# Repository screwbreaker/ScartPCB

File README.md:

# ScartPCB
A little PCB to buld a SCART cable for console and old computers

### Summary
This is a little PCB made to make easy to assemble a SCART cable for console and old computers.

### History
As anyone else I always made my SCART cables by hand, using THT components. And by soldering them directly on the SCART connector.
And that's pefectly fine. Except for systems like the Mega Drive, that require a lot of componets to be fitted in a small space.
So I thought to build a little PCB that fit inside the SCART connector in oder to make everything more easy and clean.

As example here a comparison between my old handmade cable, and the new one with this PCB:

Of course, there are other project like this around. But none of them have all the stuff I wanted.
My requirements was a buffer for the csync and a boost converter for the 12V.

My original plan was to make a PCB for each console.
But, I managed this PCB in a way that can be used almost in any case.
With this PCB is possible to make a SCART cable for almost every console and computer. It is pretty versatile.
And is made to fit inside the cheapest SCART connectors available online.

### Basic informations
The components value in the schematic and in the BOM are for a PAL Mega Drive.
For other systems, refer to the SCART diagram of the secific system.

### How it work
The PCB allow to put components in series and in parallel with the signals.
This allow to use this PCB to buld almost any SCART cable for almost any system.

To make a Mega Drive cable is necessary to put a 220uF capacitor in series with the RGB signals, since is really complicated to find small, and cheap SMD capacitors of this value, the PCB allow to put multiple capacitors in parallel. So, to make a 220uF capacitor is possible to put two 100uF 1206 plus one 22uF 0603.
Probably the 22uF are not really required, but I found the space for some extra footprint in the PCB, so the total value can be easily adjusted.

For example to make a SNES cable put a 0 ohm resistor in place of RR1, RG1, RB1, and place a 75 ohm resitor to ground on each singal by using RR2, RG2, RB2.

If you have a mono audio, like in the first model of Mega Drive, is possible to close the MONO jumper, this short toghether the left and right channel.

The video buffer is there mostly for the Mega Drive, it is nor required on most of the other systems.
To bypass the video buffer, close the NOBUF jumper, in this case do not populate any components on the buffer section.

The RGB jumper can be left open on systems that don't have an RGB output, like a C64.

In general, choose the components to match what do you need to make your video cable. By using 0 ohm resistors as jumper is possible to make almost any combination.

### Csync buffer
The Mega Drive have a problem with the csync signal.
The csync is connected to the input pin of the encoder, not to the output pin.
This can cause some issue on some TV sets. That's why I placed a buffer on the line.

The csync on the Mega Drive is also a TTL level signal, to compensate this a 300-470 ohm reistor can be placed in series with the signal to reduce the voltage to something more like to the standard.
Most of the time also a 220uF capacitor in series with the signal is required.
Not only the Mega Drive use a TTL signal on the csync, it cab be present also on other systems.

Unfortunately not all TV do like this values for the csync line.
So, the values can be adjusted to match your TV set requirements.
Be careful with the level of the signals, they must be in a range that do not cause any damage to your TV.

The values on the csync line, that are on the schematic or in the BOM are for a PAL Mega Drive.
With this set of components I can use my modded MD on my TV, by switching from PAL to NTSC withouth any issue.

Other systems don't have this issue.
The buffer can be bypassed if not needed by closing the NOBUF jumper.
In this case, do not populate any component on the buffer section.

### 12V booster
There is a little boost converter to step up the 5V and get the 12V required for the 4:3 aspect ration.
This is the only way to have the switch voltage.
Some systems, like Amiga or SNES do have the 12V on the connector. But, due to the small space on the PCB, is not possible to use it.

### BOM
The BOM is for a PAL Mega Drive.
To make SCART cables for other system choose the components according to the specific schematic.
Use 0 ohm resistors as jumper where needed.

For the boost converter TPS61040DBVR and TPS61041DBVR are equivalent for this application.

For the buffer any pair of complementary transistors can be used, the package must be SC-70 or equivalent.

### PCB Manufacturing
Unfortunately, due to the space constraints inside the SCART connector, this PCB is a 4 layer board.
And for the same reason, some components are 0402.

The PCB still very cheap to produce, since it is very small, and it use standard vias and traces.

Soldering 0402 components by hand require a bit of skill on soldering.

### Bonus
All the SCART connectors I bought have an hawful issue. The cable gland, the plastic thing that close the SCART shell, is made out the most brittle material in the world.
Initially, I thought that this was because I bought the cheapest SCART connector available on internet.
However even the ones bought on trusth resellers or on electronic shops have this issue.
So, I made a replacement that can be 3D printed. It's far to be perfect, I have no skills on 3D printing. But it do the job.

### License
The PCBs are under the CERN OHL license.
The firmwares, under the GPL3.

This is an OPEN project.
So, like any other project like this, the hope is that others can improve it an reshare with the community.
Don't go out this basic guideline.

### Disclaimer
The hardware and the software are provided to you 'as is' and without any express or implied warranties whatsoever with respect to its functionality, operability or use, including, without limitation, any implied warranties of merchantability, fitness for a particular purpose or infringement. We expressly disclaim any liability whatsoever for any direct, indirect, consequential, incidental or special damages, including, without limitation, lost revenues, lost profits, losses resulting from business interruption or loss of data, regardless of the form of action or legal theory under which the liability may be asserted, even if advised of the possibility or likelihood of such damages.

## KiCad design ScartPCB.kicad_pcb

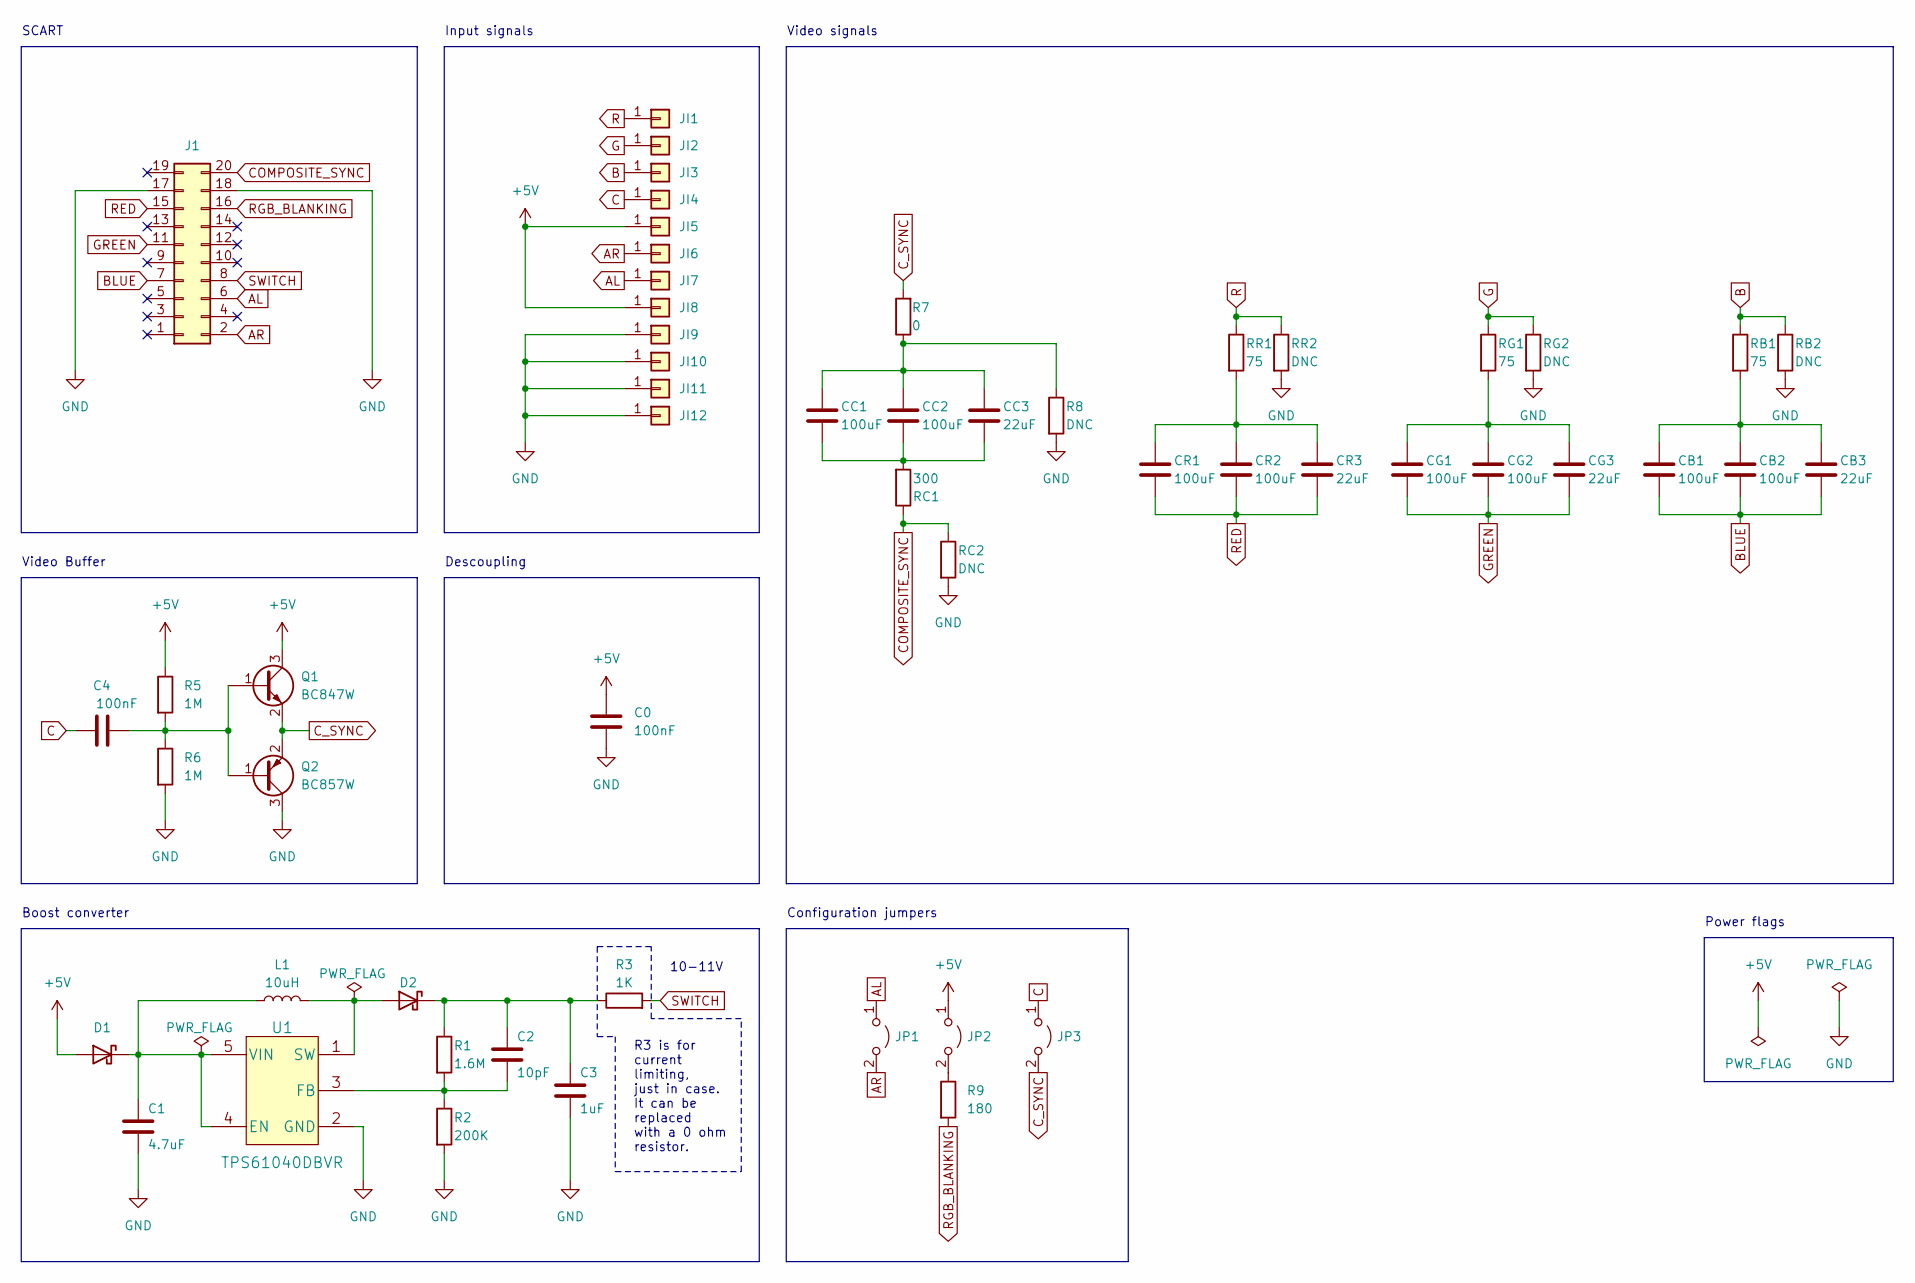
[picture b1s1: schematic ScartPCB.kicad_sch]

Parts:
C0, C4: 100nF; C_0402_1005Metric; Manufacturer_Part_Number CC0402KRX7R7BB104
C1: 4.7uF; C_0402_1005Metric; Manufacturer_Part_Number CM05X5R475M25AH
C2: 10pF; C_0402_1005Metric; Manufacturer_Part_Number 0402N100J500CT
C3: 1uF; C_0402_1005Metric; Manufacturer_Part_Number GRM155R61E105MA12D
CB1, CB2: 100uF; C_1206_3216Metric; Manufacturer_Part_Number GRM31CR61A107ME05L
CB3: 22uF; C_0603_1608Metric; Manufacturer_Part_Number CL10A226MP8NUNE
CC1, CC2: 100uF; C_1206_3216Metric; Manufacturer_Part_Number GRM31CR61A107ME05L
CC3: 22uF; C_0603_1608Metric; Manufacturer_Part_Number CL10A226MP8NUNE
CG1, CG2: 100uF; C_1206_3216Metric; Manufacturer_Part_Number GRM31CR61A107ME05L
CG3: 22uF; C_0603_1608Metric; Manufacturer_Part_Number CL10A226MP8NUNE
CR1, CR2: 100uF; C_1206_3216Metric; Manufacturer_Part_Number GRM31CR61A107ME05L
CR3: 22uF; C_0603_1608Metric; Manufacturer_Part_Number CL10A226MP8NUNE
D1, D2: D_Schottky; D_0402_1005Metric; Manufacturer_Part_Number CDBQR0130R-HF
J1: Conn_02x10_Odd_Even; SCART
JI1, JI2, JI3, JI4, JI5, JI6, JI7, JI8, JI9, JI10, JI11, JI12: Conn_01x01; PAD2x2
JP1, JP2, JP3: Jumper_2_Open; SolderJumper-2_P1.3mm_Open_TrianglePad1.0x1.5mm
L1: 10uH; L_0603_1608Metric; Manufacturer_Part_Number MLZ1608M100WT000
Q1: BC847W; SOT-323_SC-70; Manufacturer_Part_Number BC847W,115
Q2: BC857W; SOT-323_SC-70; Manufacturer_Part_Number BC857W,135
R1: 1.6M; R_0402_1005Metric; Manufacturer_Part_Number RC0402FR-071M6L
R2: 200K; R_0402_1005Metric; Manufacturer_Part_Number 0402WGF2003TCE
R3: 1K; R_0402_1005Metric; Manufacturer_Part_Number 0402WGF1001TCE
R5, R6: 1M; R_0402_1005Metric; Manufacturer_Part_Number 0402WGF1004TCE
R7: 0; R_0402_1005Metric; Manufacturer_Part_Number 0402WGF750JTCE
R8: DNC; R_0402_1005Metric
R9: 180; R_0402_1005Metric; Manufacturer_Part_Number HP02WAF1800TCE
RB1: 75; R_0402_1005Metric; Manufacturer_Part_Number 0402WGF750JTCE
RB2: DNC; R_0402_1005Metric; Manufacturer_Part_Number 0402WGF750JTCE
RC1: 300; R_0402_1005Metric; Manufacturer_Part_Number RC0402JR-07300RL
RC2: DNC; R_0402_1005Metric
RG1: 75; R_0402_1005Metric; Manufacturer_Part_Number 0402WGF750JTCE
RG2: DNC; R_0402_1005Metric; Manufacturer_Part_Number 0402WGF750JTCE
RR1: 75; R_0402_1005Metric; Manufacturer_Part_Number 0402WGF750JTCE
RR2: DNC; R_0402_1005Metric; Manufacturer_Part_Number 0402WGF750JTCE
U1: TPS61040DBVR; Manufacturer_Part_Number TPS61040DBVR

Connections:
+5V: C0.1, D1.2 (A), JI5.1, JI8.1, JP2.1 (A), Q1.3 (C), R5.1
AL: J1.6, JI7.1, JP1.1 (A)
AR: J1.2, JI6.1, JP1.2 (B)
B: JI3.1, RB1.1, RB2.1
BLUE: CB1.2, CB2.2, CB3.2, J1.7
C: C4.1, JI4.1, JP3.1 (A)
COMPOSITE_SYNC: J1.20, RC1.1, RC2.1
C_SYNC: JP3.2 (B), Q1.2 (E), Q2.2 (E), R7.2
G: JI2.1, RG1.1, RG2.1
GND: C0.2, C1.2, C3.2, J1.17, J1.18, JI9.1, JI10.1, JI11.1, JI12.1, Q2.3 (C), R2.2, R6.2, R8.2, RB2.2, RC2.2, RG2.2, RR2.2, U1.2 (GND)
GREEN: CG1.2, CG2.2, CG3.2, J1.11
unnamed: C1.1, D1.1 (K), L1.1, U1.4 (EN), U1.5 (VIN)
unnamed: C2.1, C3.1, D2.1 (K), R1.1, R3.1
unnamed: C2.2, R1.2, R2.1, U1.3 (FB)
unnamed: C4.2, Q1.1 (B), Q2.1 (B), R5.2, R6.1
unnamed: CB1.1, CB2.1, CB3.1, RB1.2
unnamed: CC1.1, CC2.1, CC3.1, RC1.2
unnamed: CC1.2, CC2.2, CC3.2, R7.1, R8.1
unnamed: CG1.1, CG2.1, CG3.1, RG1.2
unnamed: CR1.1, CR2.1, CR3.1, RR1.2
unnamed: D2.2 (A), L1.2, U1.1 (SW)
unnamed: JP2.2 (B), R9.1
R: JI1.1, RR1.1, RR2.1
RED: CR1.2, CR2.2, CR3.2, J1.15
RGB_BLANKING: J1.16, R9.2
SWITCH: J1.8, R3.2

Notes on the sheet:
Configuration jumpers
Power flags
Boost converter
Descoupling
Video Buffer
SCART
Input signals
10-11V
Video signals
R3 is for current limiting, just in case. It can be replaced with a 0 ohm resistor.

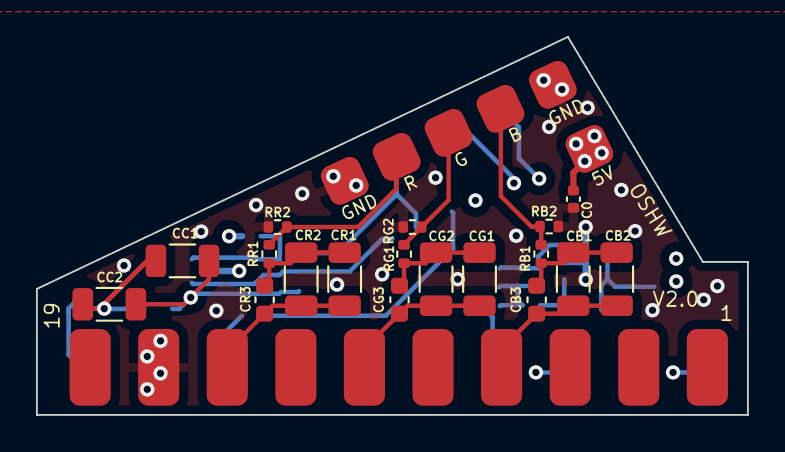
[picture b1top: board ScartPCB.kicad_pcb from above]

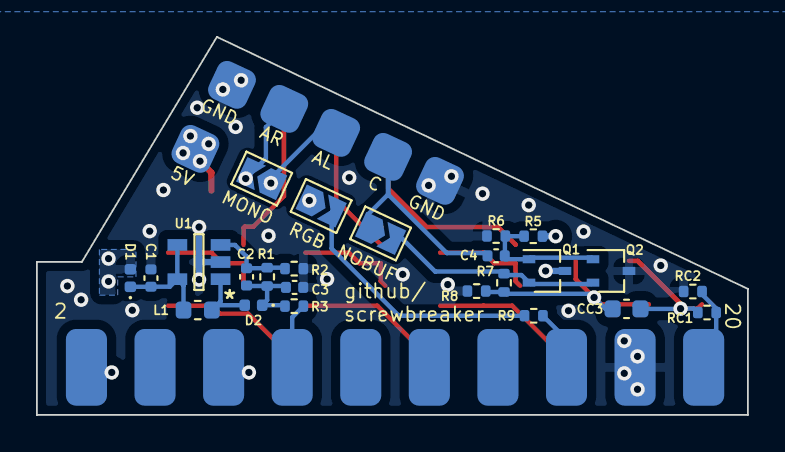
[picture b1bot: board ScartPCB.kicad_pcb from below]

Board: 4 copper layers, 39.5 x 21.0 mm, 55 parts (30 on the bottom side), 26 nets.

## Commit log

2023-12-03 Create deleteme
2024-07-02 Add files via upload
    Updated schematics
